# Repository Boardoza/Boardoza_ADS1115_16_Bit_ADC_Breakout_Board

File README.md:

# Boardoza ADS1115 16-Bit ADC Breakout Board

The **Boardoza ADS1115 Breakout Board** is a high-resolution analog-to-digital conversion module based on the **Texas Instruments ADS1115 16-bit ADC**. It features four configurable analog input channels that support both single-ended and differential measurements. With its integrated programmable gain amplifier (PGA), internal voltage reference, and low-noise architecture, the board enables accurate analog signal acquisition for embedded systems and sensor applications.

The board operates with a **3.3V to 5V power supply** and communicates through an **I²C interface**, making it compatible with Arduino, Raspberry Pi, ESP32, STM32, and other microcontroller platforms. The board is suitable for **precision sensor monitoring, voltage measurement, data acquisition, and industrial control applications**.

---

## PCB Pictures

| Front Side | Back Side |
| :---: | :---: |
|  |  |

---

## Key Features

- **16-Bit ADC Resolution:** Provides high-resolution analog-to-digital conversion for precise sensor and voltage measurements.
- **Flexible Analog Inputs:** Supports four single-ended inputs or two differential measurements through a configurable input multiplexer.
- **I²C Communication Interface:** Enables easy integration with microcontrollers using a two-wire communication interface.
- **Programmable Gain Amplifier (PGA):** Supports selectable full-scale input ranges for measuring signals of different amplitudes.
- **Low-Power Operation:** Supports single-shot and continuous conversion modes for energy-efficient measurement applications.

---

## Technical Specifications

**Model:** ADS1115  
**Manufacturer:** Boardoza  
**Manufacturer IC:** Texas Instruments  
**Input Voltage:** 3.3V - 5V  
**Interface:** I²C  
**Resolution:** 16-bit  
**Analog Input Channels:** 4 Single-Ended or 2 Differential  
**Programmable Data Rate:** 8SPS - 860SPS  
**Internal Reference:** Integrated Voltage Reference  
**Operating Modes:** Single-Shot and Continuous Conversion  
**Operating Temperature:** -40°C to +125°C  
**Board Dimensions:** 20mm x 40mm  

> **Note:** The programmable full-scale range does not represent the maximum allowable voltage on the analog input pins. Input voltages must remain within the ADS1115 supply limits.

---

## Board Pinout

### ( J1 ) Power Supply and I²C Communication Pins

| Pin Number | Pin Name | Description |
| :---: | :---: | --- |
| 1 | VIN | Power Supply Input (3.3V - 5V) |
| 2 | ALERT | Programmable Comparator Output or Conversion-Ready Signal |
| 3 | SDA | I²C Serial Data Line |
| 4 | SCL | I²C Serial Clock Line |
| 5 | GND | Ground Connection |

### ( J2 ) Analog Input Pins

| Pin Number | Pin Name | Description |
| :---: | :---: | --- |
| 1 | AIN3 | Analog Input 3. |
| 2 | AIN2 | Analog Input 2. |
| 3 | AIN1 | Analog Input 1. |
| 4 | AIN0 | Analog Input 0. |

---

## Board Dimensions

---

## Step Files

[Boardoza ADS1115.step](./assets/ADS1115%20Step.step)

---

## Datasheet

[ADS1115 Datasheet.pdf](./assets/ADS1115%20Datasheet.pdf)

---

## Version History

- V1.0.0 - Initial Release

---

## Support

- If you have any questions or need support, please contact <support@boardoza.com>

---

## **License**

This repository contains both hardware and software components:

### **Hardware Design**

[![CC BY-SA 4.0][cc-by-sa-shield]][cc-by-sa]

All hardware design files are licensed under [Creative Commons Attribution-ShareAlike 4.0 International License][cc-by-sa].

[cc-by-sa]: http://creativecommons.org/licenses/by-sa/4.0/
[cc-by-sa-shield]: https://img.shields.io/badge/License-CC%20BY--SA%204.0-lightgrey.svg

### **Software/Firmware**

[![BSD-3-Clause][bsd-shield]][bsd]

All software and firmware are licensed under [BSD 3-Clause License][bsd].

[bsd]: https://opensource.org/licenses/BSD-3-Clause
[bsd-shield]: https://img.shields.io/badge/License-BSD%203--Clause-blue.svg

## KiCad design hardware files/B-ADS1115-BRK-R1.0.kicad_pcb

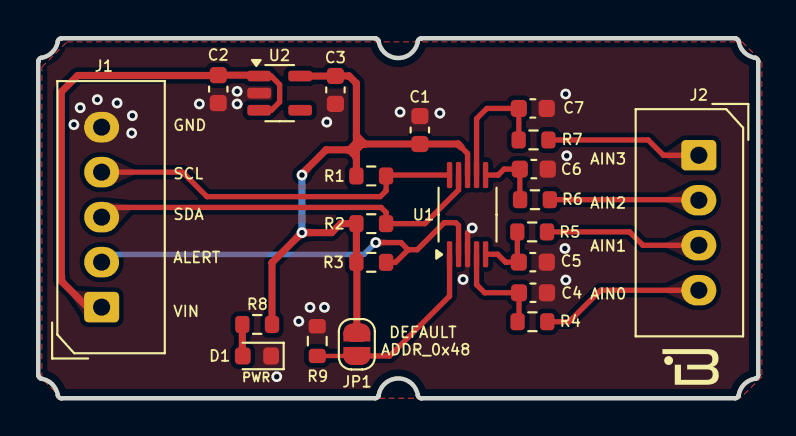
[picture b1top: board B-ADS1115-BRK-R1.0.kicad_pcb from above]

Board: 2 copper layers, 40.0 x 20.0 mm, 22 parts (0 on the bottom side), 16 nets.

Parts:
C1, C4, C5, C6, C7: 100nF; C_0603_1608Metric
C2: 1uF; C_0603_1608Metric
C3: 2.2uF; C_0603_1608Metric
D1: LED; LED_0603_1608Metric
J1: Conn_01x05; 2317-05S_1x05_P2.50mm_Vertical
J2: Conn_01x04; 2317-04S_1x04_P2.50mm_Vertical
JP1: SolderJumper_2_Open; SolderJumper-2_P1.3mm_Open_RoundedPad1.0x1.5mm
R1, R2, R3, R9: 10k; R_0603_1608Metric
R4, R5, R6, R7: 0; R_0603_1608Metric
R8: 470; R_0603_1608Metric
U1: ADS1115; VSSOP-10_3x3mm_P0.5mm
U2: LP2980-N; SOT-23-5

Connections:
/AIN0: J2.4, R4.2
/AIN0I: C4.1, R4.1, U1.4 (AIN0)
/AIN1: J2.3, R5.2
/AIN1I: C5.1, R5.1, U1.5 (AIN1)
/AIN2: J2.2, R6.2
/AIN2I: C6.1, R6.1, U1.6 (AIN2)
/AIN3: J2.1, R7.2
/AIN3I: C7.1, R7.1, U1.7 (AIN3)
/ALERT_RDY: J1.2, R3.1, U1.2 (ALERT_RDY)
/SCL: J1.4, R1.2, U1.10 (SCL)
/SDA: J1.3, R2.2, U1.9 (SDA)
/VDD: C1.2, C3.1, JP1.2 (B), R1.1, R2.1, R3.2, R8.2, U1.8 (VDD), U2.5 (VOUT)
/VIN: C2.1, J1.1, U2.1 (VIN), U2.3 (ON/~OFF)
GND: C1.1, C2.2, C3.2, C4.2, C5.2, C6.2, C7.2, D1.1 (K), J1.5, R9.2, U1.3 (GND), U2.2 (GND)
unnamed: D1.2 (A), R8.1
unnamed: JP1.1 (A), R9.1, U1.1 (ADDR)
